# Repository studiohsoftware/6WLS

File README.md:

# 6WLS Powered Busboard
This powered busboard design features a four layer PCB with a single dedicated ground plane and EMI shielded supplies. The result is a very low noise system with unprecedented preset bus stability.
</br>
</br>
There are two versions that fit Buchla cases. A 30W version for cases 18 spaces or less, and a 40W version for 24 space cases. The only difference between them are the supplies used, and the PCB footprints to support them (the board mounting in the boat is exactly the same.) The 30W version uses the Cincon EC6C, and the 40W version uses the Cincon EC7C. These supplies can be back ordered through either mouser.com or sager.com. 
</br>
</br>
There is a 40W "OTHER" version for cases using Roman bolt spacing (SAM/BOOPS/etc.) This board also uses the Cincon EC7C.
</br>
</br>
Passive busboards on Roman bolt spacing can be ordered through Osh Park here https://oshpark.com/projects/a7F1rsy2
</br>
</br>
6WLS-40 (40W version) with Cincon EC7C supplies.

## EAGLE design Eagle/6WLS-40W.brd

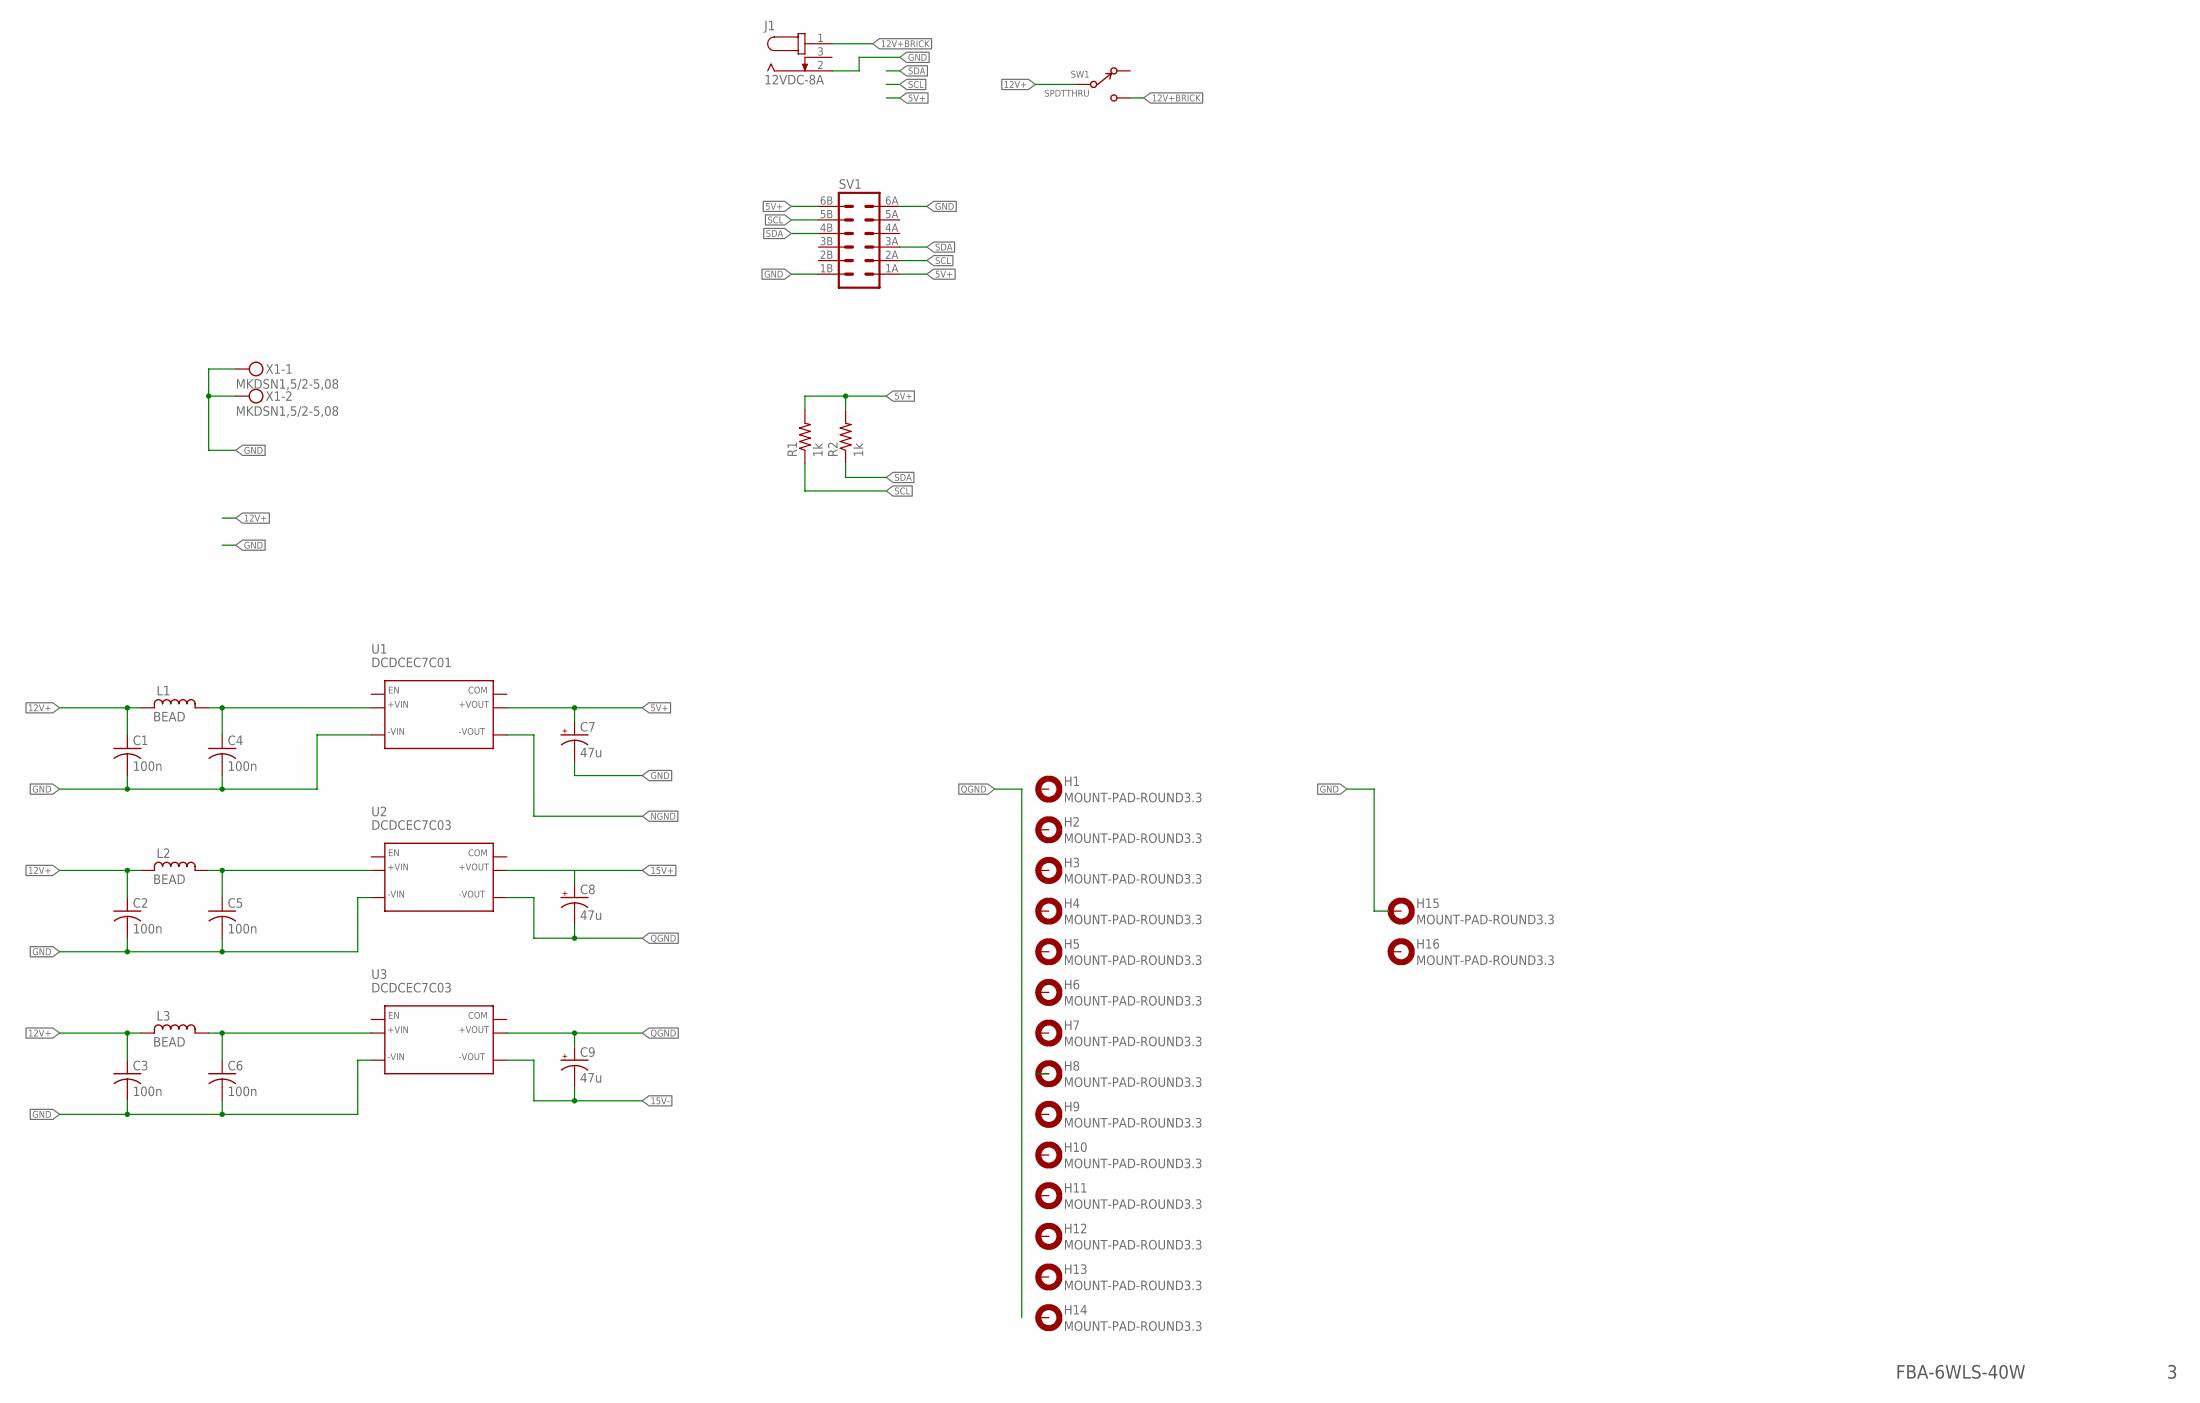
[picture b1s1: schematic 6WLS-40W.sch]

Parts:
C1, C2, C3, C4, C5, C6: 100n; C050-025X075
C7, C8, C9: 47u; E5-6
H1, H2, H3, H4, H5, H6, H7, H8, H9, H10, H11, H12, H13, H14, H15, H16: MOUNT-PAD-ROUND3.3; 3,3-PAD
J1: 12VDC-8A; BARREL
L1, L2, L3: BEAD
R1, R2: 1k; 0207/7
SV1: MA06-2CARD; EBC06DRAS
SW1: SPDTTHRU; SPDT-THRU
U1: DCDCEC7C01; EC7C
U2, U3: DCDCEC7C03; EC7C
X1: MKDSN1,5/2-5,08

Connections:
5V+: C7.+, R1.2, R2.2, SV1.1A (1), SV1.6B (12), U1.S+ (+VOUT), U1.VO+ (+VOUT)
12V+: C1.1, C2.1, C3.1, L1.1, L2.1, L3.1, SW1.C
12V+BRICK: J1.1, SW1.1
15V+: C8.+, U2.S+ (+VOUT), U2.VO+ (+VOUT)
15V-: C9.-, U3.S- (-VOUT), U3.VO- (-VOUT)
COM: U1.NC (COM), U2.NC (COM), U3.NC (COM)
GND: C1.2, C2.2, C3.2, C4.2, C5.2, C6.2, C7.-, H15.B3,3, J1.2, SV1.1B (2), SV1.6A (11), U1.VIN- (-VIN), U2.VIN- (-VIN), U3.VIN- (-VIN), X1.1, X1.2
unnamed: C5.1, L2.2 (4), U2.VIN+ (+VIN)
unnamed: C6.1, L3.2 (4), U3.VIN+ (+VIN)
unnamed: C4.1, L1.2 (4), U1.VIN+ (+VIN)
NGND: U1.S- (-VOUT), U1.VO- (-VOUT)
QGND: C8.-, C9.+, U2.S- (-VOUT), U2.VO- (-VOUT), U3.S+ (+VOUT), U3.VO+ (+VOUT)
SCL: R1.1, SV1.2A (3), SV1.5B (10)
SDA: R2.1, SV1.3A (5), SV1.4B (8)

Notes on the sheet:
FBA-6WLS-40W

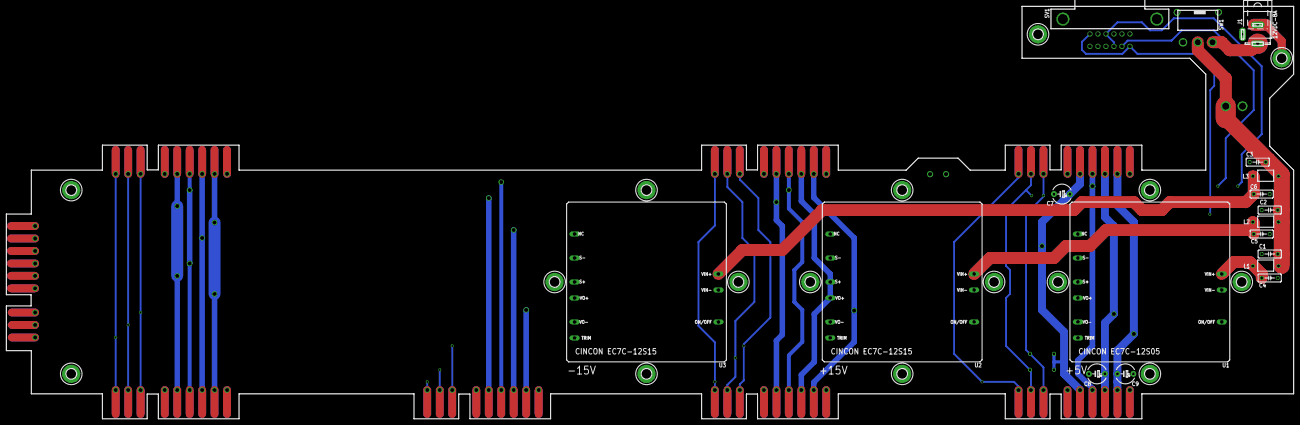
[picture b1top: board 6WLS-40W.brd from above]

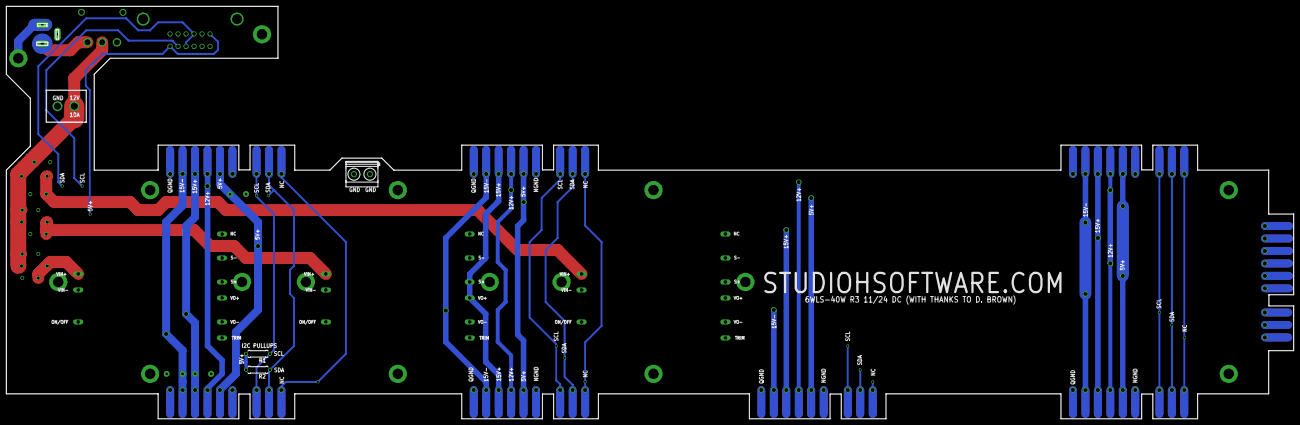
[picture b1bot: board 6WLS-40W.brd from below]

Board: 4 copper layers, 409.3 x 131.1 mm, 37 parts (3 on the bottom side), 14 nets.

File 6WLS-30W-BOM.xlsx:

Qty | Value | Parts | Description | MF | MPN
1 |  | SV1 | PIN HEADER (mount with two 4-40 x 1/2" machine screws) | SULLINS | EBC06DRAS
6 | 100n | C1, C2, C3, C4, C5, C6 | Ceramic CAPACITOR
1 | 12VDC-8A | J1 | DC POWER JACK | TENSILITY | 54-00167
2 | 1k | R1, R2 | RESISTOR
3 | 47u | C7, C8, C9 | POLARIZED ALUM CAPACITOR
3 | BEAD | L1, L2, L3 | Inductor | LAIRD | 28L0138-80R-10
1 | DCDCMULT6 | U1 | 5V DCDC Converter | Cincon | EC6C01
2 | DCDCMULT6 | U2, U3 | 15V DCDC Converter (see also Recom/Delta alternates on PCB) | Cincon | EC6C03
1 | SPDTTHRU | SW1 | SPDT Switch | NKK | MS13ASG30
1 | MKDSN | MKDSN | Terminal Block | PHOENIX | 1729128

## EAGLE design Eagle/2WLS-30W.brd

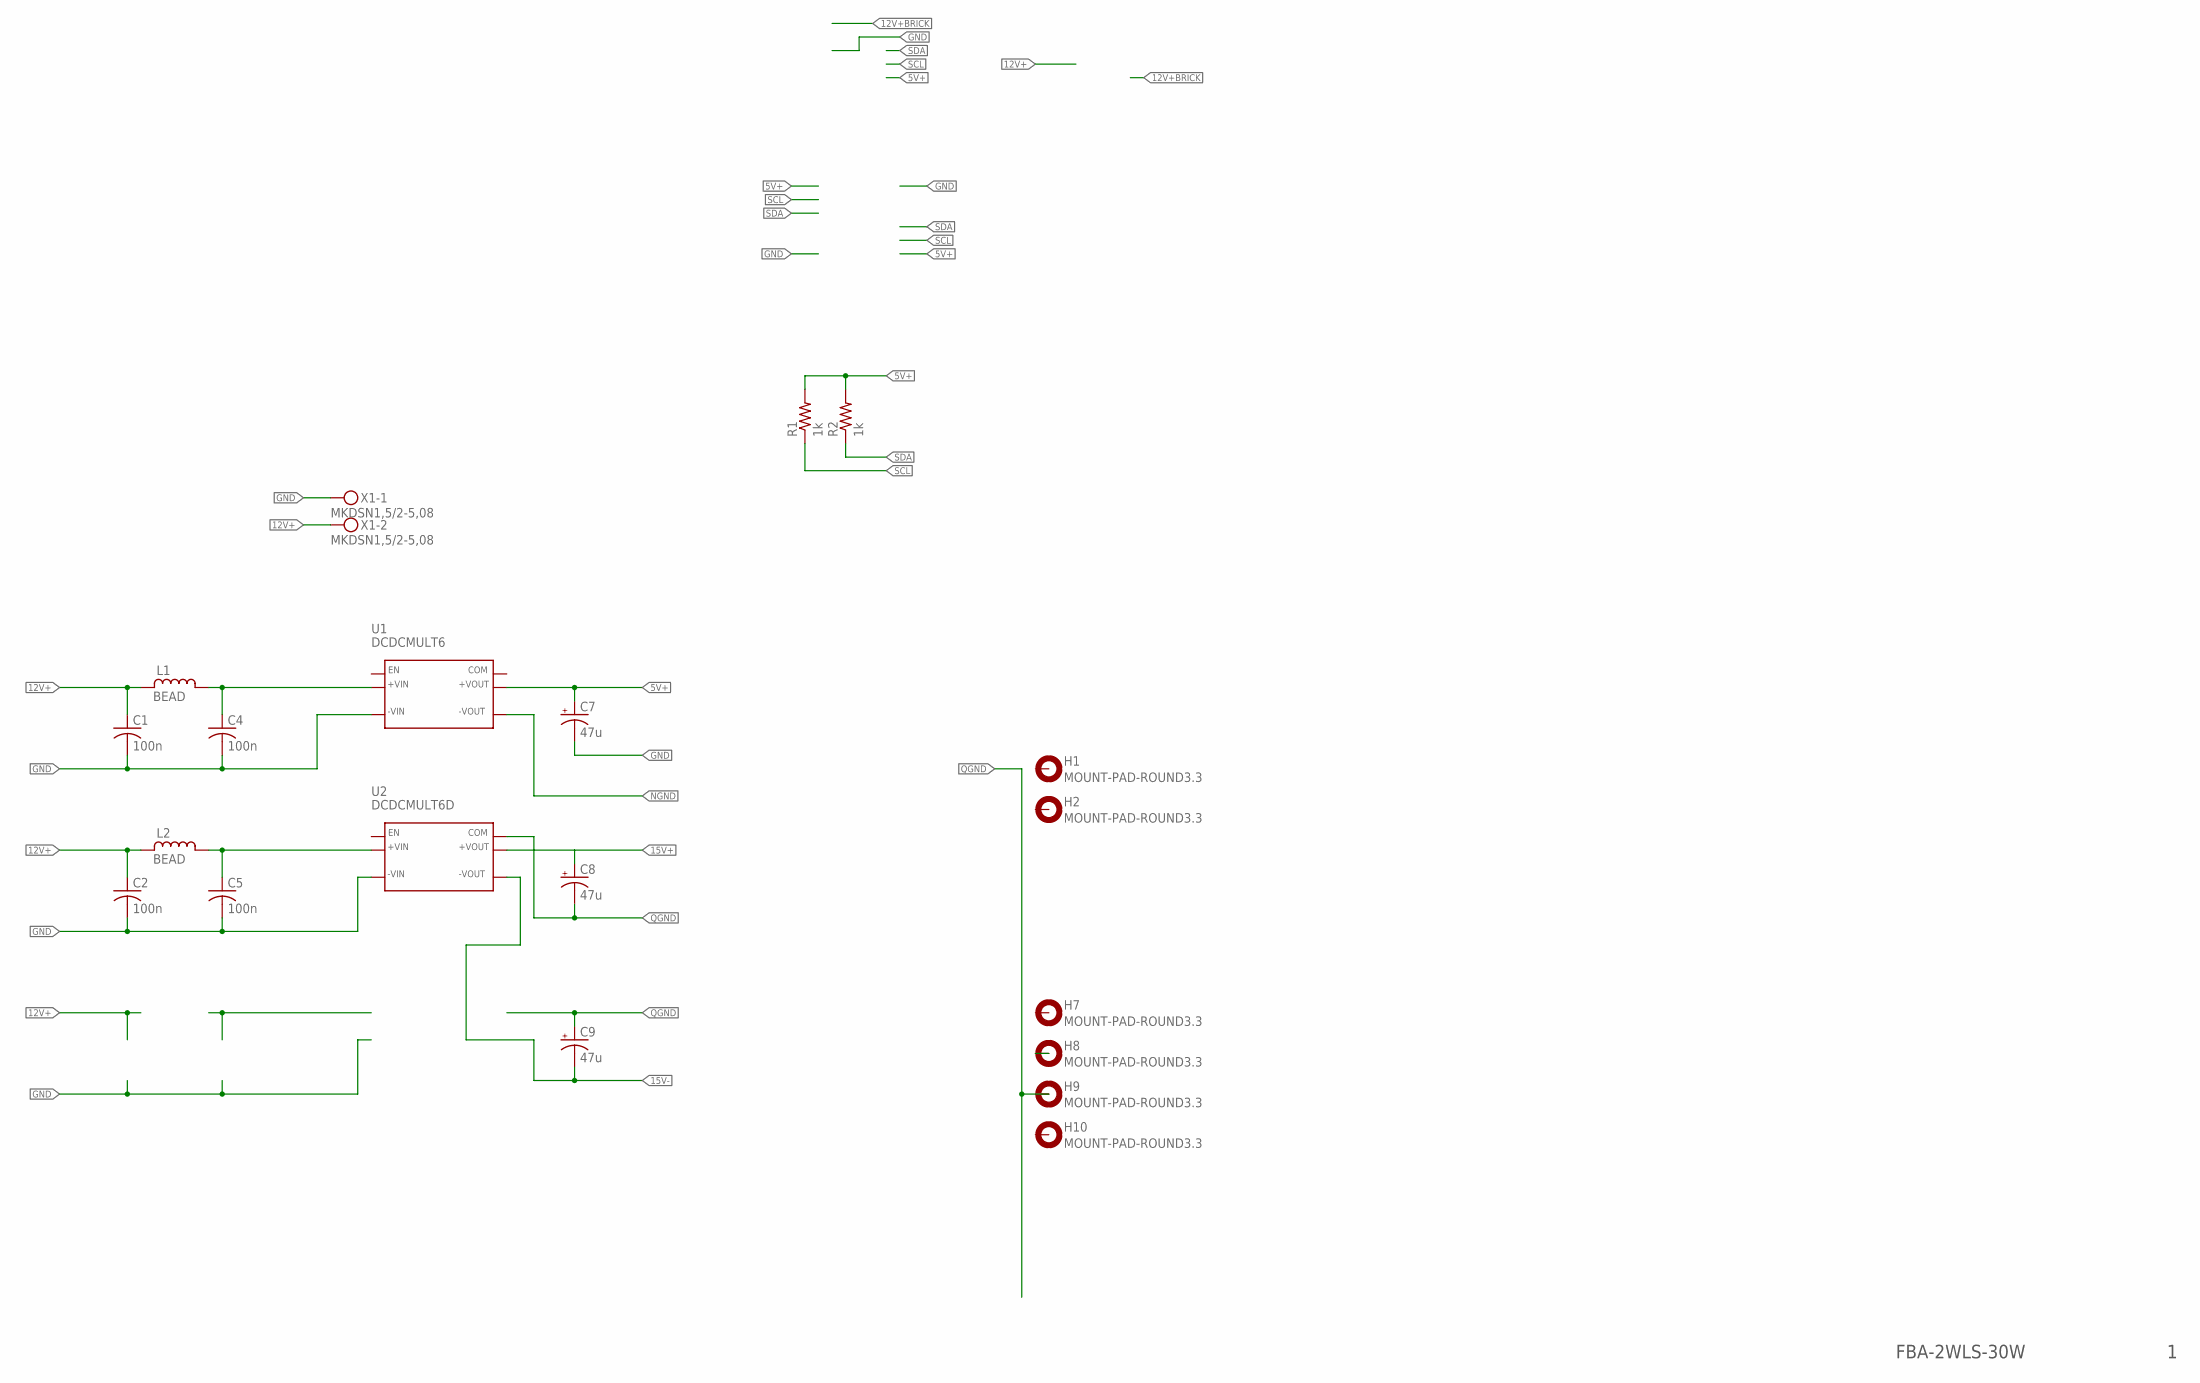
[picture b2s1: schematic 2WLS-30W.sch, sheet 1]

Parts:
C1, C2, C4, C5: 100n; C050-025X075
C7, C8, C9: 47u; E5-6
H1, H2, H7, H8, H9, H10: MOUNT-PAD-ROUND3.3; 3,3-PAD
L1, L2: BEAD
R1, R2: 1k; 0207/7
U1: DCDCMULT6; EC6CMULT
U2: DCDCMULT6D; EC6CMULTD
X1: MKDSN1,5/2-5,08

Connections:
5V+: C7.+, R1.2, R2.2, U1.VO1+ (+VOUT), U1.VO+ (+VOUT)
12V+: C1.1, C2.1, L1.1, L2.1, X1.2
15V+: C8.+, U2.VO1+ (+VOUT), U2.VO+ (+VOUT)
15V-: C9.-, U2.VO1- (-VOUT), U2.VO- (-VOUT)
COM: U1.TRIM (COM), U1.TRIM1 (COM)
GND: C1.2, C2.2, C4.2, C5.2, C7.-, U1.VIN1- (-VIN), U1.VIN- (-VIN), U2.VIN1- (-VIN), U2.VIN- (-VIN), X1.1
unnamed: C5.1, L2.2 (4), U2.VIN1+ (+VIN), U2.VIN+ (+VIN)
unnamed: C4.1, L1.2 (4), U1.VIN1+ (+VIN), U1.VIN+ (+VIN)
NGND: U1.VO1- (-VOUT), U1.VO- (-VOUT)
QGND: C8.-, C9.+, U2.COM, U2.COM1 (COM)
SCL: R1.1
SDA: R2.1

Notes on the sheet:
FBA-2WLS-30W

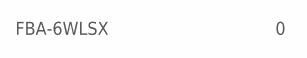
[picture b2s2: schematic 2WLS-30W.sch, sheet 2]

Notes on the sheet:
FBA-6WLSX

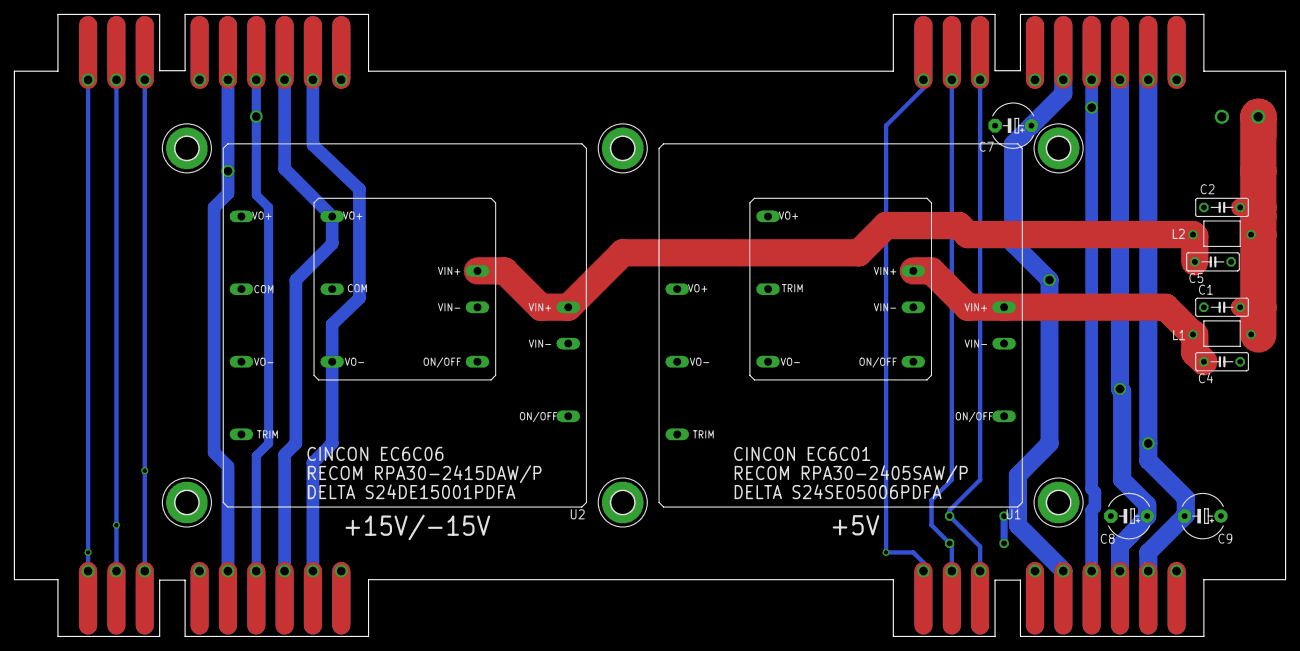
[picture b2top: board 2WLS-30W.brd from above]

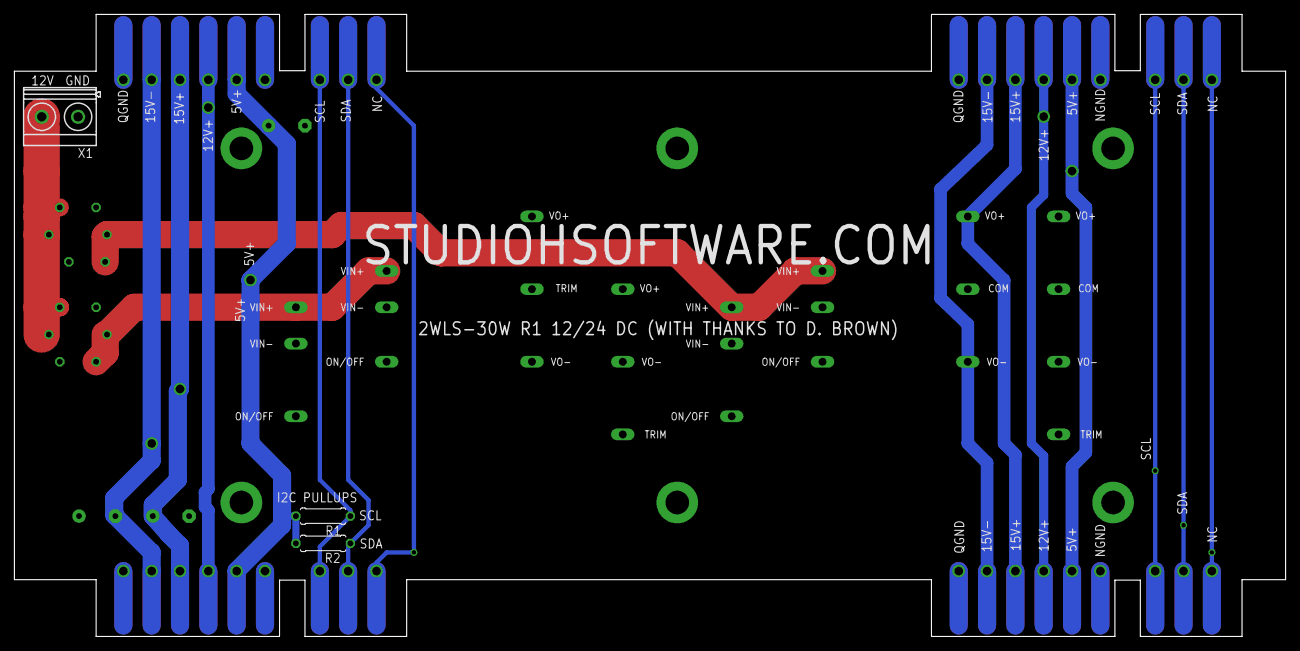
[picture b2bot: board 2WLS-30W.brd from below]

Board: 4 copper layers, 177.8 x 87.0 mm, 20 parts (3 on the bottom side), 10 nets.

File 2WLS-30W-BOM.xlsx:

Qty | Value | Parts | Description | MF | MPN
4 | 100n | C1, C2, C4, C5 | Ceramic CAPACITOR
2 | 1k | R1, R2 | RESISTOR
3 | 47u | C7, C8,C9 | POLARIZED ALUM CAPACITOR
2 | BEAD | L1, L2 | Inductor | LAIRD | 28L0138-80R-10
1 | DCDCMULT6 | U1 | 5V DCDC Converter | Cincon | EC6C01
1 | DCDCMULT6D | U2 | 15V DCDC Dual Converter | Cincon | EC6C06
1 | MKDSN | MKDSN | Terminal Block | PHOENIX | 1729128

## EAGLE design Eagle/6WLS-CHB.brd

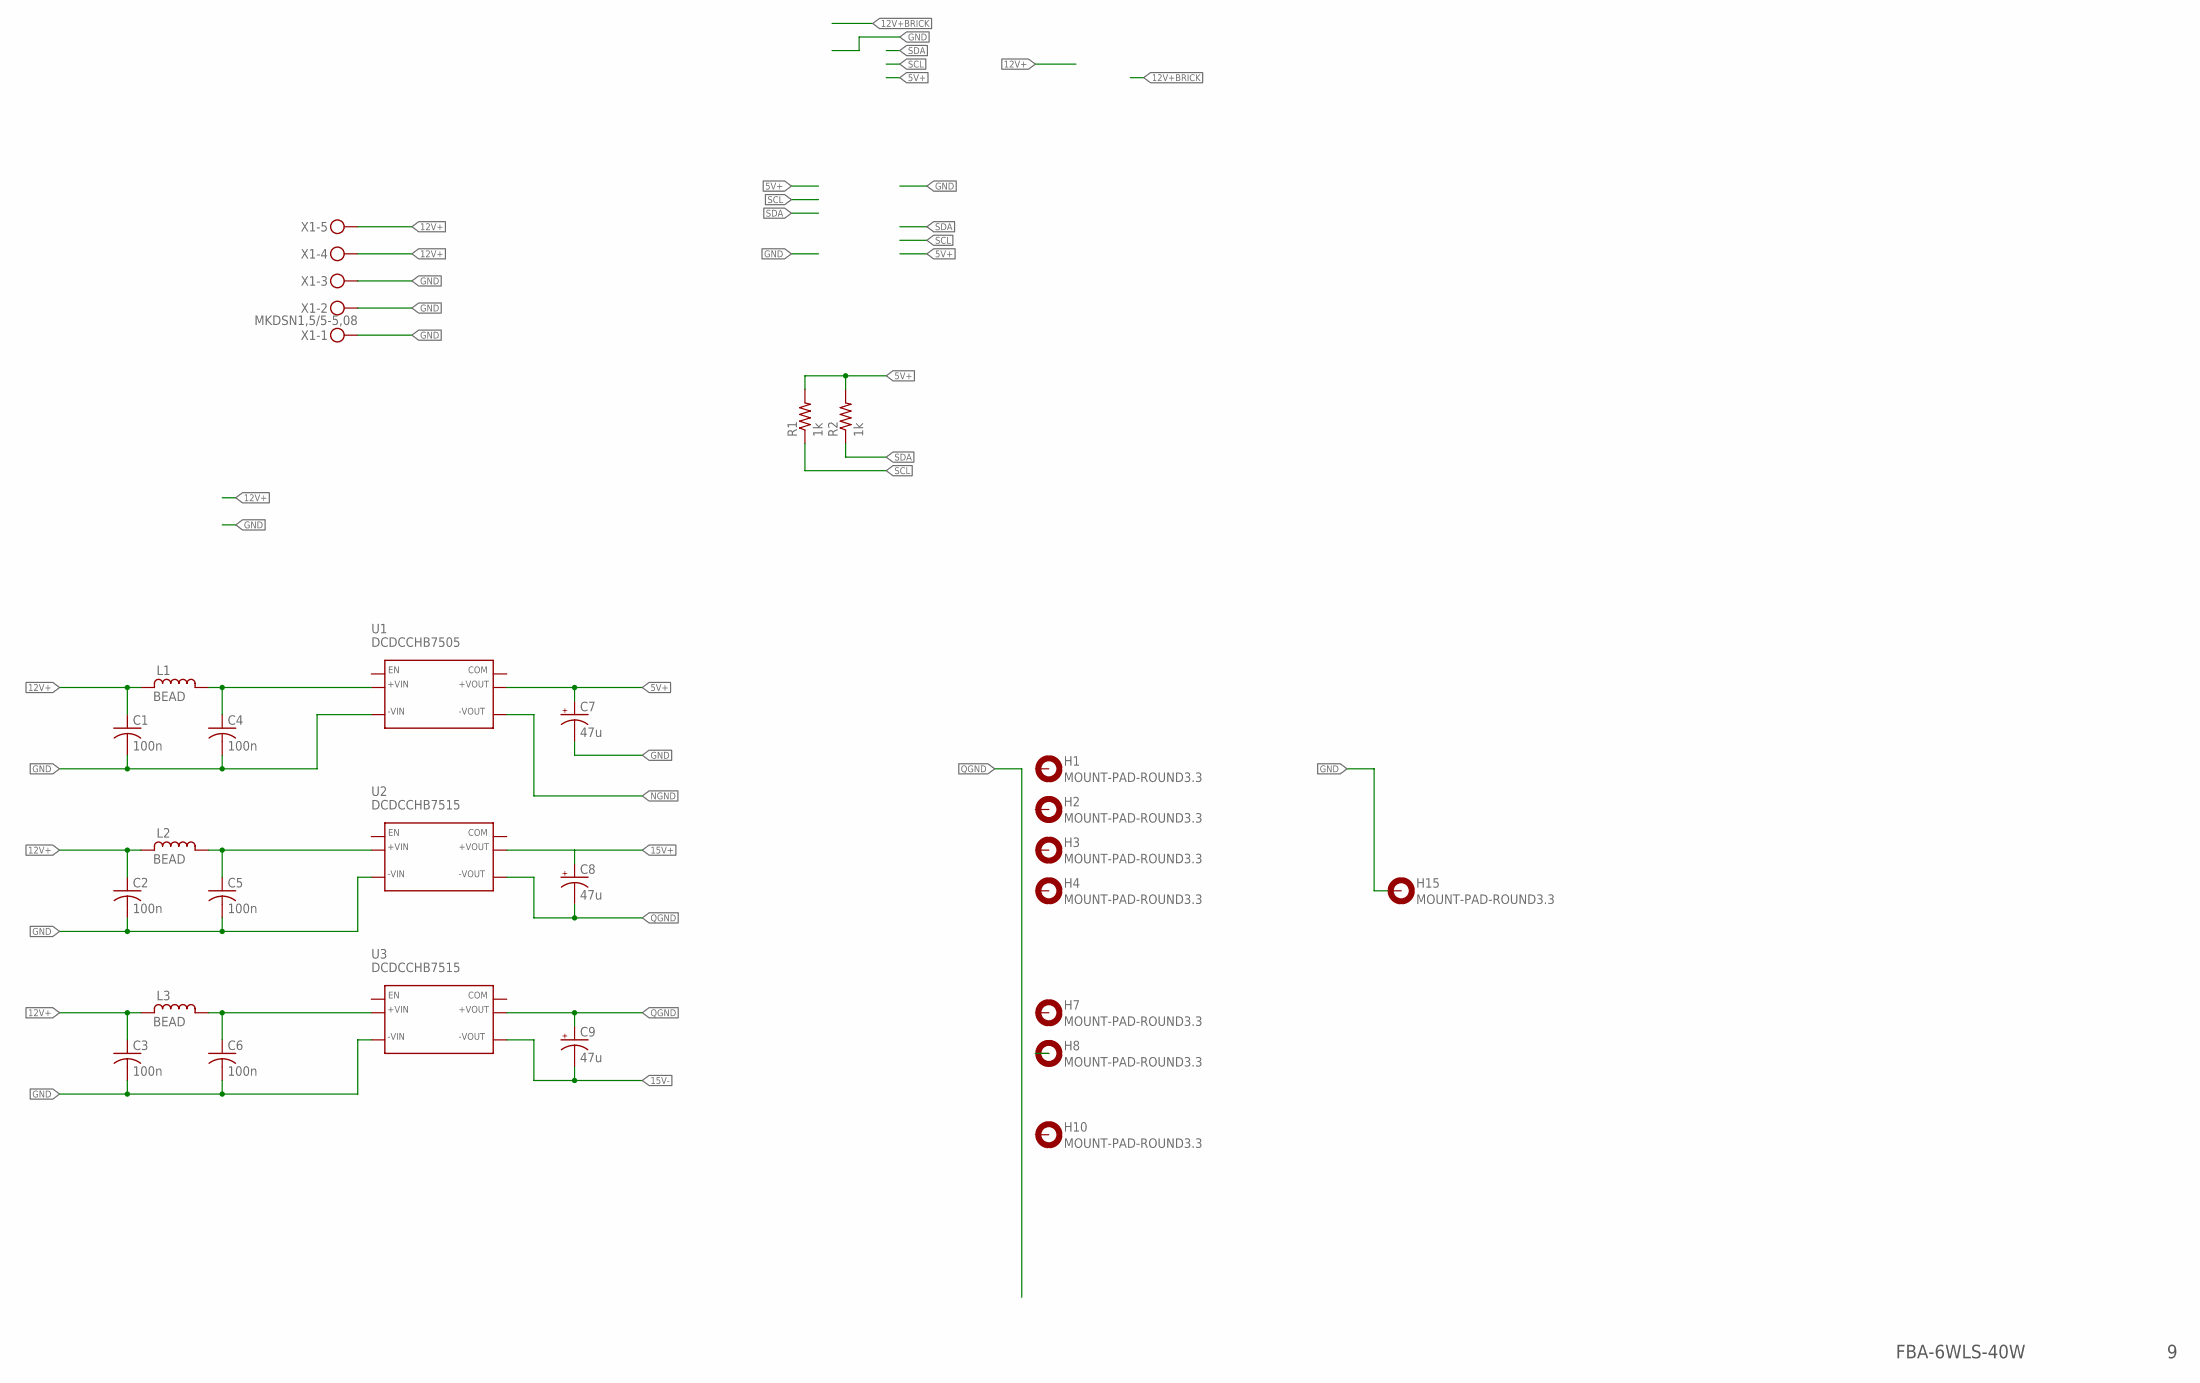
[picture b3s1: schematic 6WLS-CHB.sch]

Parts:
C1, C2, C3, C4, C5, C6: 100n; C050-025X075
C7, C8, C9: 47u; E5-6
H1, H2, H3, H4, H7, H8, H10, H15: MOUNT-PAD-ROUND3.3; 3,3-PAD
L1, L2, L3: BEAD
R1, R2: 1k; 0207/7
U1: DCDCCHB7505; DCDC2
U2, U3: DCDCCHB7515; DCDC2
X1: MKDSN1,5/5-5,08

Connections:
5V+: C7.+, R1.2, R2.2, U1.SEN+ (+VOUT), U1.VO+ (+VOUT)
12V+: C1.1, C2.1, C3.1, L1.1, L2.1, L3.1, X1.4, X1.5
15V+: C8.+, U2.SEN+ (+VOUT), U2.VO+ (+VOUT)
15V-: C9.-, U3.SEN- (-VOUT), U3.VO- (-VOUT)
COM: U1.CASE (COM), U2.CASE (COM), U3.CASE (COM)
GND: C1.2, C2.2, C3.2, C4.2, C5.2, C6.2, C7.-, H15.B3,3, U1.VIN- (-VIN), U2.VIN- (-VIN), U3.VIN- (-VIN), X1.1, X1.2, X1.3
unnamed: C5.1, L2.2 (4), U2.VIN+ (+VIN)
unnamed: C6.1, L3.2 (4), U3.VIN+ (+VIN)
unnamed: C4.1, L1.2 (4), U1.VIN+ (+VIN)
NGND: U1.SEN- (-VOUT), U1.VO- (-VOUT)
QGND: C8.-, C9.+, U2.SEN- (-VOUT), U2.VO- (-VOUT), U3.SEN+ (+VOUT), U3.VO+ (+VOUT)
SCL: R1.1
SDA: R2.1

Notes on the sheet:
FBA-6WLS-40W

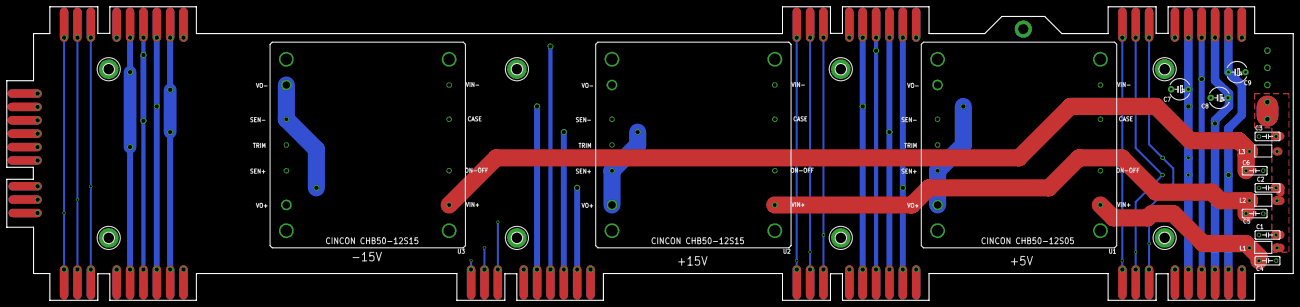
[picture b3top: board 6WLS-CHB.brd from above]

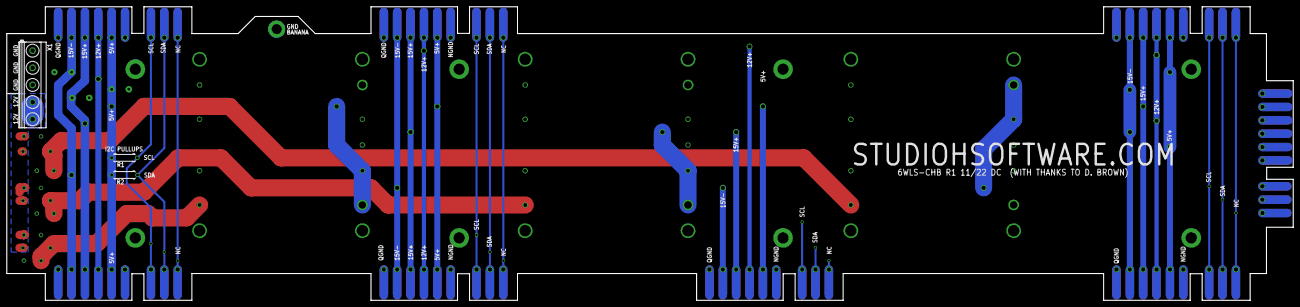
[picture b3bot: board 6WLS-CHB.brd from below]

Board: 4 copper layers, 381.3 x 87.0 mm, 26 parts (3 on the bottom side), 11 nets.

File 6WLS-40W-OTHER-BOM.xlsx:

Qty | Value | Device | Package | Parts | Description | MF | MPN | Z_DIGIKEY | Z_MOUSER
1 | MKDSN | MKDSN | MKDSN | X1 | Terminal Block | PHOENIX | 1729157 | 277-1250-ND
6 | 100n | C-US050-025X075 | C050-025X075 | C1, C2, C3, C4, C5, C6 | CAPACITOR, American symbol
2 | 1k | R-US_0207/7 | 0207/7 | R1, R2 | RESISTOR, American symbol
3 | 47u | CPOL-USE5-6 | E5-6 | C7, C8, C9 | POLARIZED CAPACITOR, American symbol
3 | BEAD | L | BEAD | L1, L2, L3 | Inductor | LAIRD | 28L0138-80R-10 | 240-2513-2-ND
1 | DCDCEC7C01 | DCDCEC7C01 | EC7C | U1 | DCDC Converter | CINCON | EC7C-12S05
2 | DCDCEC7C03 | DCDCEC7C03 | EC7C | U2, U3 | DCDC Converter | CINCON | EC7C-12S15

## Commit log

2022-05-27 Add BOM
2022-06-19 Add images of 30W board.
2022-08-16 Add 40W Eagle files.
2022-08-16 Add 40W board images.
2022-09-28 Add Gerber ZIP Files
    Gerber files for 30 Watt version and 40 Watt version.
2022-09-28 Add BOM files.
2022-09-28 Update BOM
2022-09-28 Create Gerbers Directory
2022-09-28 Add Gerber ZIP Files
2022-12-06 Add CHB Design
2022-12-10 Bigger terminal block.
2023-01-10 Update CHB images.
2023-01-20 Add photos of 40W board.
2023-01-28 Add passive boards for Roman/SAM/Boops/etc.
2023-03-07 Move supplies down to clear upper mounting screws.
2023-03-07 Move supplies down to clear mounting screws.
2023-03-16 Add 6WLS-40W-OTHER for ROMAN/SAM/BOOPS/etc.
2023-10-18 Added files for 2WLS passive board.
2023-10-18 Add 2WLS-PASSIVE
2024-11-30 Add more copper for supply pins.
2024-11-30 Add terminal block for ground banana.
2024-11-30 Add copper for supply pins.
2024-11-30 Add drill files.
2024-12-05 Add 2WLS design, terminal blocks for ground banana
    New board 2WLS-30W for The Beast UK two space boat. Also add terminal blocks for ground bananas on Buchla format 30W and 40W boards. Correct filename on OTHER BOM.
2024-12-05 Add board for two space boat.
    New board 2WLS-30W for The Beast UK two space boat.
2024-12-05 Delete 6WLS-40W.brd
    Wrong directory
2024-12-05 Delete 6WLS-40W.sch
    Wrong directory
2024-12-05 Delete 6WLS-40W-OTHER.brd
    Wrong directory
2024-12-05 Delete 6WLS-40W-OTHER.sch
    Wrong directory
2024-12-05 Delete 6WLS-40W-OTHER.xlsx
    Renamed to 6WLS-40W-OTHER-BOM.xlsx
2024-12-05 Larger copper pads for supply pins.
    Switch to larger, oblong pads for supply pins. Thanks to Prism Circuits.
2024-12-05 Add board for two space boat.
    Add new board 2WLS-30W for The Beast UK two space boat. Also larger copper pad size for supply pins on 6WLS-30W board.
2025-05-02 Fix quantities on 2WLS-30W-BOM
2025-05-23 Add 2WLS EXTENDER and fix 2WLS PASSIVE solder mask
2025-05-23 Add 2WLS EXTENDER and fix 2WLS PASSIVE silkscreen
2025-06-28 Adjust dimensions to fit Keen case.
2025-12-06 Fix silkscreen
